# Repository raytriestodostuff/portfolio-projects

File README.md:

# HELLO! : ) - Engineering portfolio 
Please read the `portfolio_overview.pdf` for project specific details.

Project source files can be found in the `projects` subfolder

## Complete project list:
Last updated:29/09/2025

1. Dual DC motor driver - Designed in Altium Desinger 
2. STM32 Microcontroller clone - Designed in Ki-Cad
3. USB LI-PO battery charger - Designed in Altium Desinger
4. Mentric EMDR light therapy bar
5. Schematic capture for ESP32 dev board

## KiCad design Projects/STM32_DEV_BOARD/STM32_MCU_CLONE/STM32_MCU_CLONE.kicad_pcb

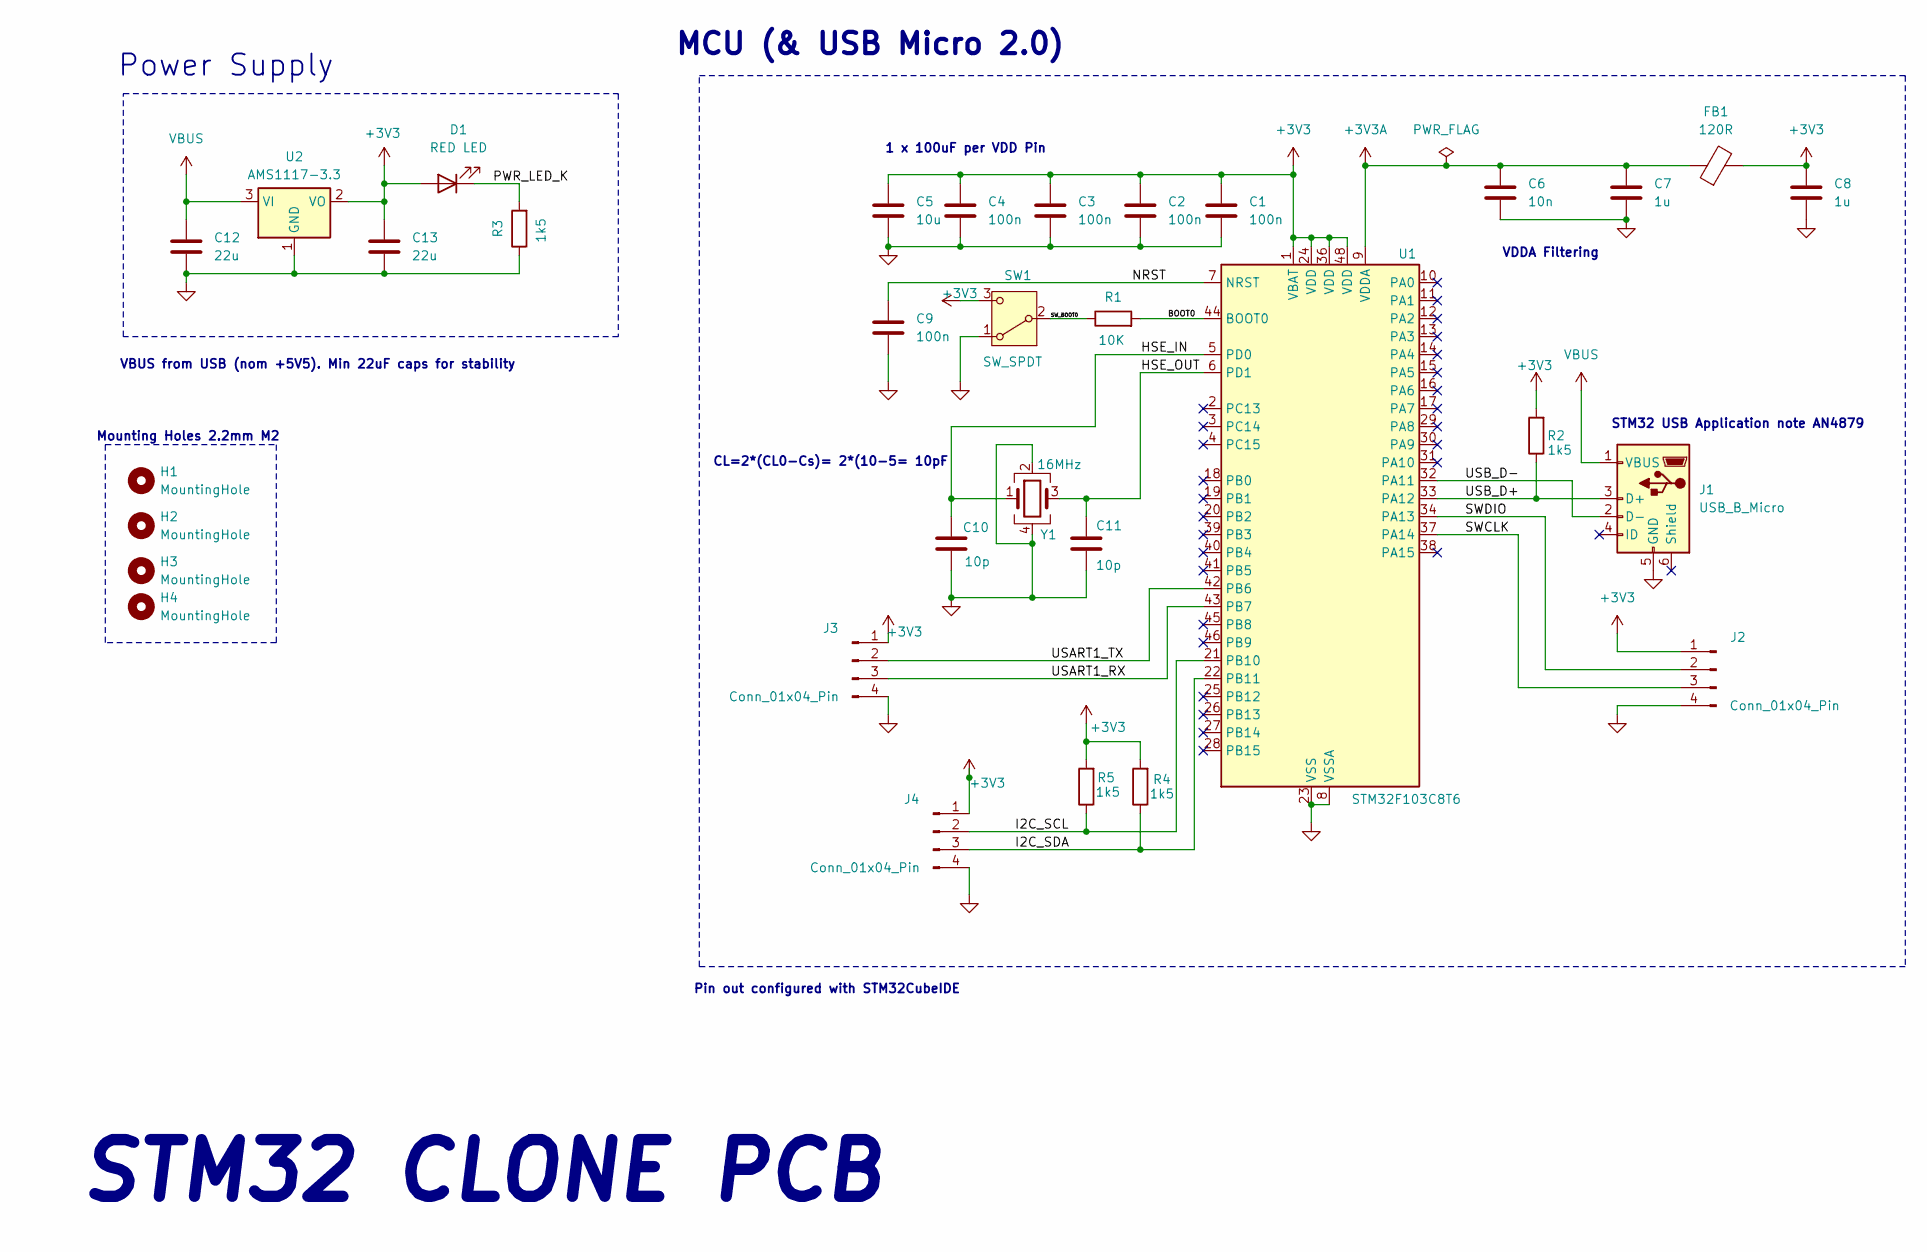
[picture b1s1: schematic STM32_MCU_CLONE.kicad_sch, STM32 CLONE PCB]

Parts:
C1, C2, C3, C4, C9: 100n; C_0805_2012Metric
C5: 10u; C_0805_2012Metric
C6: 10n; C_0805_2012Metric
C7, C8: 1u; C_0805_2012Metric
C10, C11: 10p; C_0805_2012Metric
C12, C13: 22u; C_0805_2012Metric
D1: RED LED; LED_0805_2012Metric
FB1: 120R; L_0805_2012Metric
H1, H2, H3, H4: MountingHole; MountingHole_2.2mm_M2
J1: USB_B_Micro; USB_Micro-B_Wuerth_629105150521
J2, J3, J4: Conn_01x04_Pin; PinHeader_1x04_P2.54mm_Vertical
R1: 10K; R_0805_2012Metric
R2, R3, R4, R5: 1k5; R_0805_2012Metric
SW1: SW_SPDT; SW_SPDT_PCM12
U1: STM32F103C8T6; LQFP-48_7x7mm_P0.5mm
U2: AMS1117-3.3; SOT-223-3_TabPin2
Y1: 16MHz; Crystal_SMD_3225-4Pin_3.2x2.5mm

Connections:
+3V3: C1.1, C2.1, C3.1, C4.1, C5.1, C8.1, C13.1, D1.2 (A), FB1.2, J2.1, J3.1, J4.1, R2.2, R4.2, R5.2, SW1.3 (C), U1.1 (VBAT), U1.24 (VDD), U1.36 (VDD), U1.48 (VDD), U2.2 (VO)
+3V3A: C6.1, C7.1, FB1.1, U1.9 (VDDA)
/BOOT0: R1.2, U1.44 (BOOT0)
/HSE_IN: C10.1, U1.5 (PD0), Y1.1
/HSE_OUT: C11.1, U1.6 (PD1), Y1.3
/I2C_SCL: J4.2, R5.1, U1.21 (PB10)
/I2C_SDA: J4.3, R4.1, U1.22 (PB11)
/NRST: C9.1, U1.7 (NRST)
/PWR_LED_K: D1.1 (K), R3.2
/SWCLK: J2.3, U1.37 (PA14)
/SWDIO: J2.2, U1.34 (PA13)
/SW_BOOT0: R1.1, SW1.2 (B)
/USART1_RX: J3.3, U1.43 (PB7)
/USART1_TX: J3.2, U1.42 (PB6)
/USB_D+: J1.3 (D+), R2.1, U1.33 (PA12)
/USB_D-: J1.2 (D-), U1.32 (PA11)
GND: C1.2, C2.2, C3.2, C4.2, C5.2, C6.2, C7.2, C8.2, C9.2, C10.2, C11.2, C12.2, C13.2, J1.5 (GND), J2.4, J3.4, J4.4, R3.1, SW1.1 (A), U1.8 (VSSA), U1.23 (VSS), U1.35 (VSS), U1.47 (VSS), U2.1 (GND), Y1.2, Y1.4
VBUS: C12.1, J1.1 (VBUS), U2.3 (VI)

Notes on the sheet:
Mounting Holes 2.2mm M2
MCU (& USB Micro 2.0)
VDDA Filtering
VBUS from USB (nom +5V5). Min 22uF caps for stability
1 x 100uF per VDD Pin
Pin out configured with STM32CubeIDE
STM32 USB Application note AN4879
CL=2*(CL0-Cs)= 2*(10-5= 10pF
Power Supply
STM32 CLONE PCB

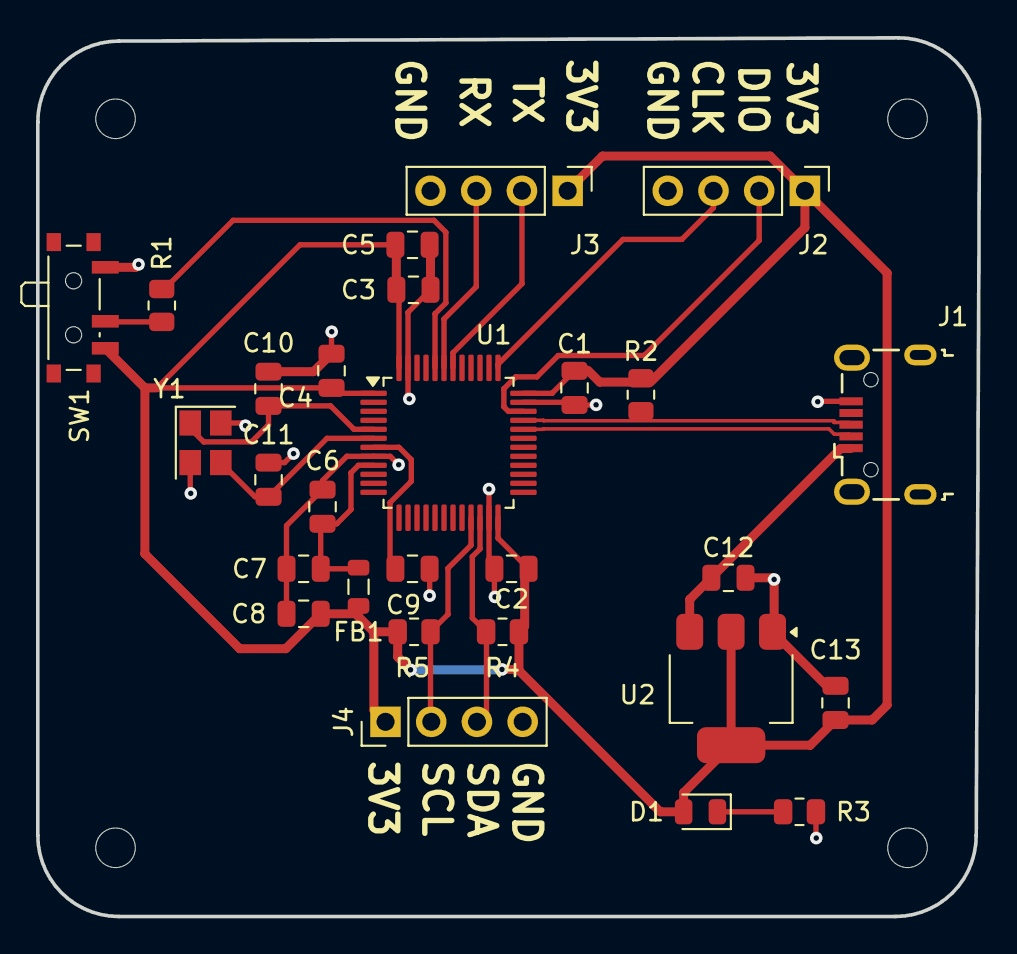
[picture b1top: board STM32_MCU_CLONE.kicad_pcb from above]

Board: 2 copper layers, 52.3 x 48.8 mm, 32 parts (0 on the bottom side), 18 nets.

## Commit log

2024-08-05 Added dual motor driver prj
2024-08-07 Pushed STM32 Prj
2024-08-07 STM32 Prj overview push
2024-08-13 Prj update
2024-08-17 doc update
